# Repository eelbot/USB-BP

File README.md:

# USB Booster Pack
## For F28069 and F28377S LaunchPads
The [TMS320F28069U](http://www.ti.com/tool/launchxl-f28069m) and  [TMS320F28377S](http://www.ti.com/tool/LAUNCHXL-F28377S) microcontrollers both have USB D+ and D- pins directly on the chip. This Booster Pack provides a Female USB B connecter as well an input selection jumper, for easier connection to the USB pins.

## Firmware Examples
TI provides many examples for these two microcontrollers in their ControlSuite software. It is freely available online [here](http://www.ti.com/tool/controlsuite).

## Note
The USB connection on the booster pack **does not** supply voltage to the LaunchPad via the 3V3 or 5V pins.

## To Do
- Final Hardware Tests (need to wait until boards arrive)

## License
<br>
This work is licensed under a [Creative Commons Attribution-ShareAlike 3.0 Unported License](http://creativecommons.org/licenses/by-sa/3.0/)

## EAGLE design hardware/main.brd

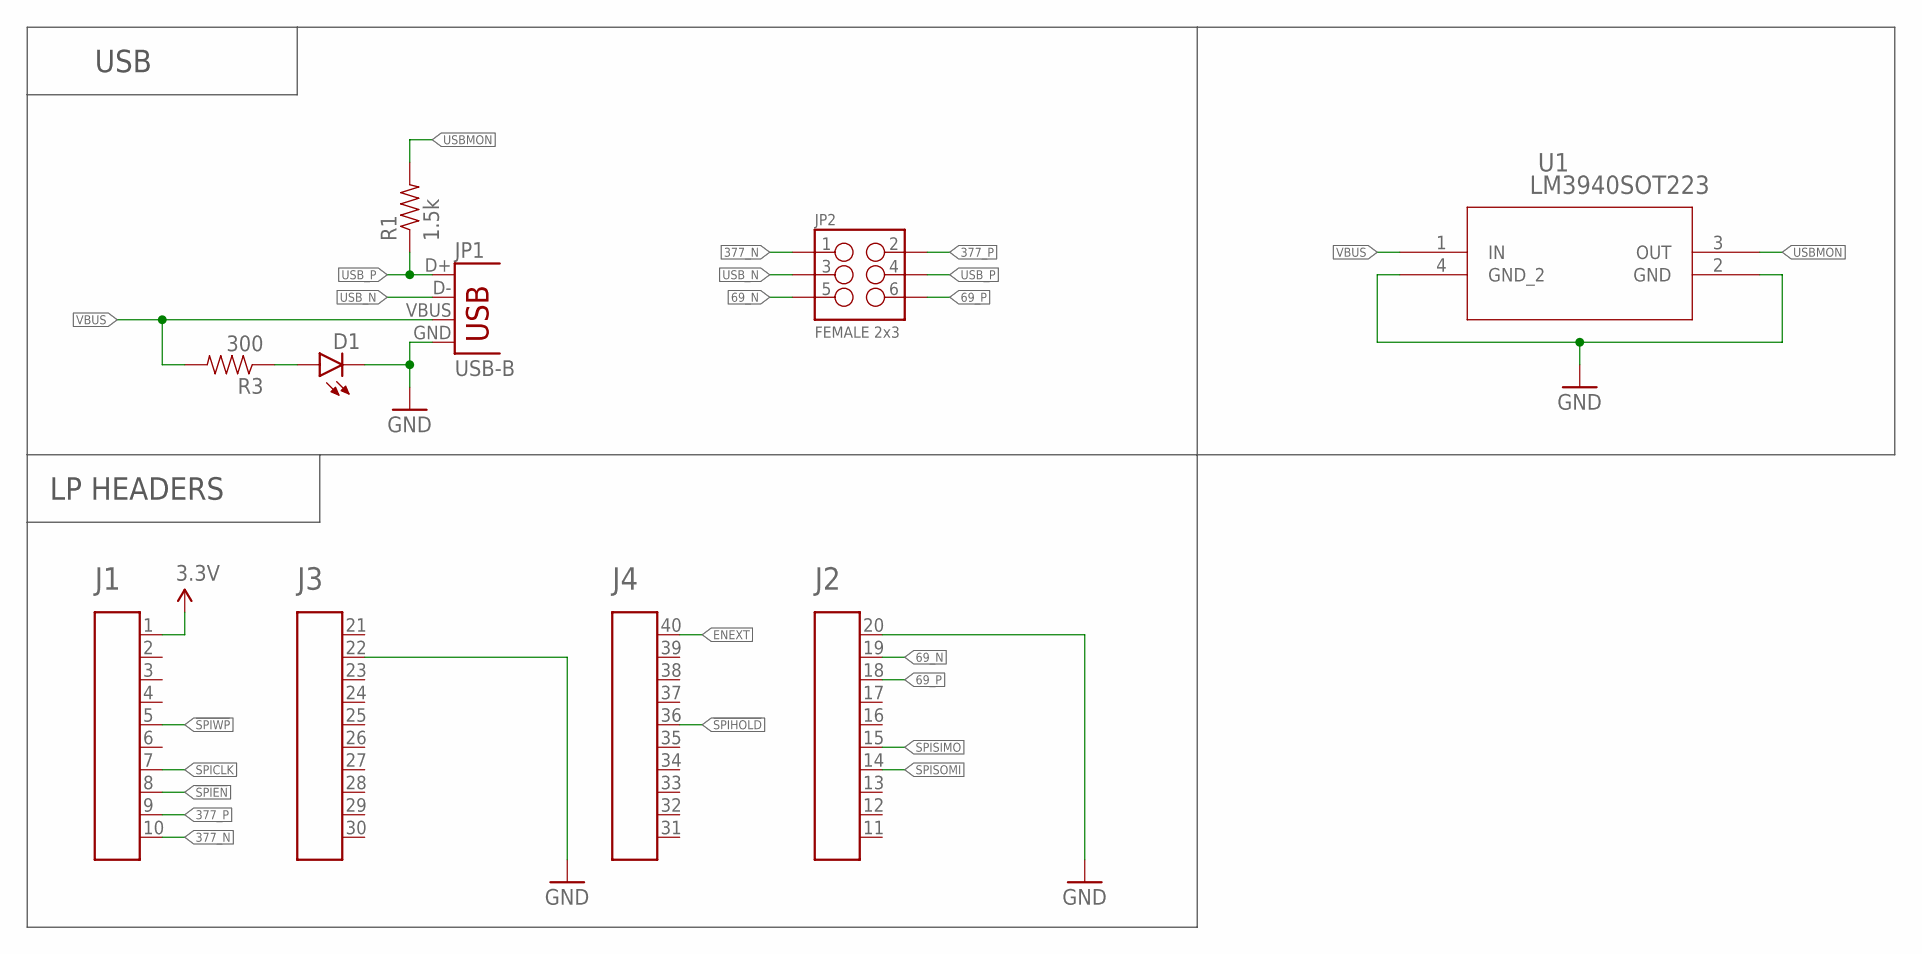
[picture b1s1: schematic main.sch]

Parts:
A1: HEADER4X10-BOOSTERPACK; 4X10-BOOSTERPACK
D1: LED3MM
JP1: USB-B; USB-B-PTH
JP2: FEMALE 2x3; 2X3
R1: 1.5k; AXIAL-0.3
R3: 300; AXIAL-0.3
U1: LM3940SOT223; DCY

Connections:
3.3V: A1.1
69_N: A1.19, JP2.5
69_P: A1.18, JP2.6
377_N: A1.10, JP2.1
377_P: A1.9, JP2.2
!SPIEN!: A1.8
!SPIHOLD!: A1.36
!SPIWP!: A1.5
ENEXT: A1.40
GND: A1.20, A1.22, D1.K (C), JP1.GND, U1.2 (GND), U1.4 (GND_2)
unnamed: D1.A, R3.P$1 (1)
SPICLK: A1.7
SPISIMO: A1.15
SPISOMI: A1.14
USBMON: R1.P$2 (2), U1.3 (OUT)
USB_N: JP1.D-, JP2.3
USB_P: JP1.D+, JP2.4, R1.P$1 (1)
VBUS: JP1.VBUS, R3.P$2 (2), U1.1 (IN)

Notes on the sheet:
LP HEADERS
USB

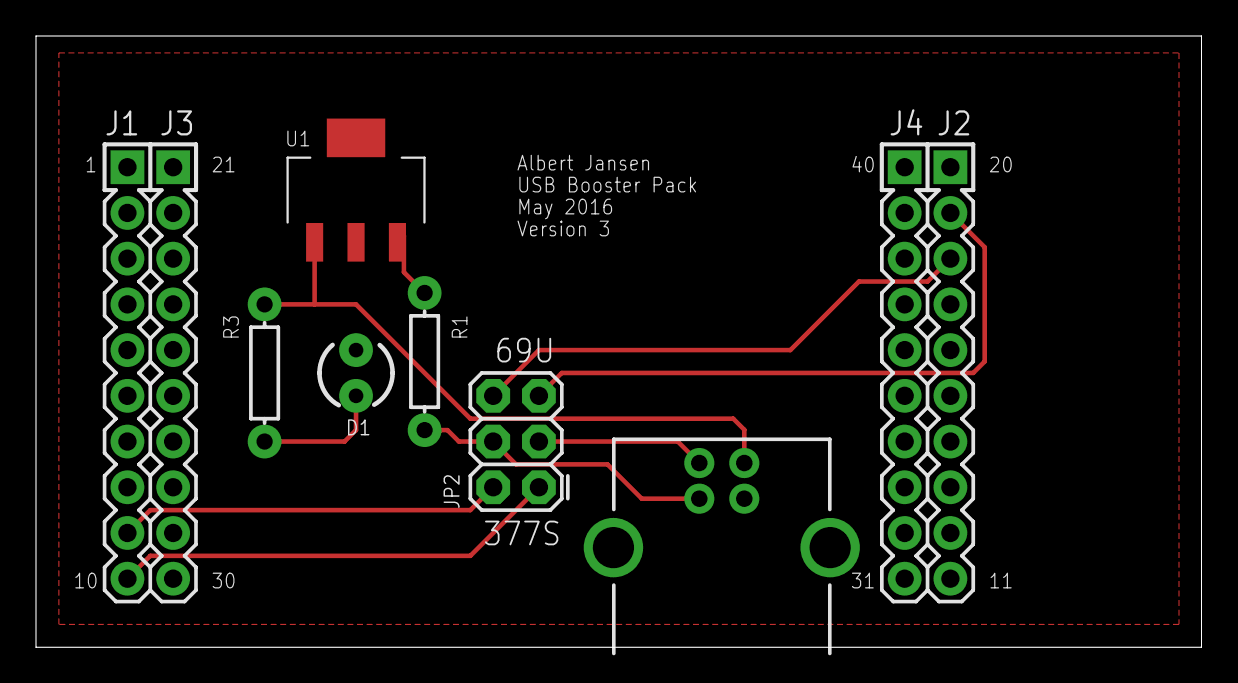
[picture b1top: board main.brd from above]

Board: 2 copper layers, 64.8 x 34.0 mm, 7 parts (0 on the bottom side), 10 nets.

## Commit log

2016-04-03 Designed schematic and routed board
2016-04-03 Added labels and cleaned up. No electrical changes
2016-04-04 Updated small labels. Cleaned up silkscreen layer.
2016-04-04 Added Name, date, version, and description
2016-04-04 Generated Gerbers - Elecrow, 2 layers
2016-04-14 Connected pullup resistor on USB
2016-04-15 Updated version number
2016-05-11 Updated routing and USB power
2016-05-11 Finalized board against DRC, added aesthetics
2016-05-16 Added generic TI USB driver
2016-05-18 Minor update to component values. Added a BOM
2016-05-20 Updated to only include hardware files: no need to add examples when TI provides them for free
2016-05-20 Added and updated documentation (with pictures!)
2016-05-20 Finalized documentation and added open source licensing and logos

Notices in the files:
parts and their libraries:
SparkFun-Connectors: Licensing: Creative Commons ShareAlike 4.0 International - https://creativecommons.org/licenses/by-sa/4.0
